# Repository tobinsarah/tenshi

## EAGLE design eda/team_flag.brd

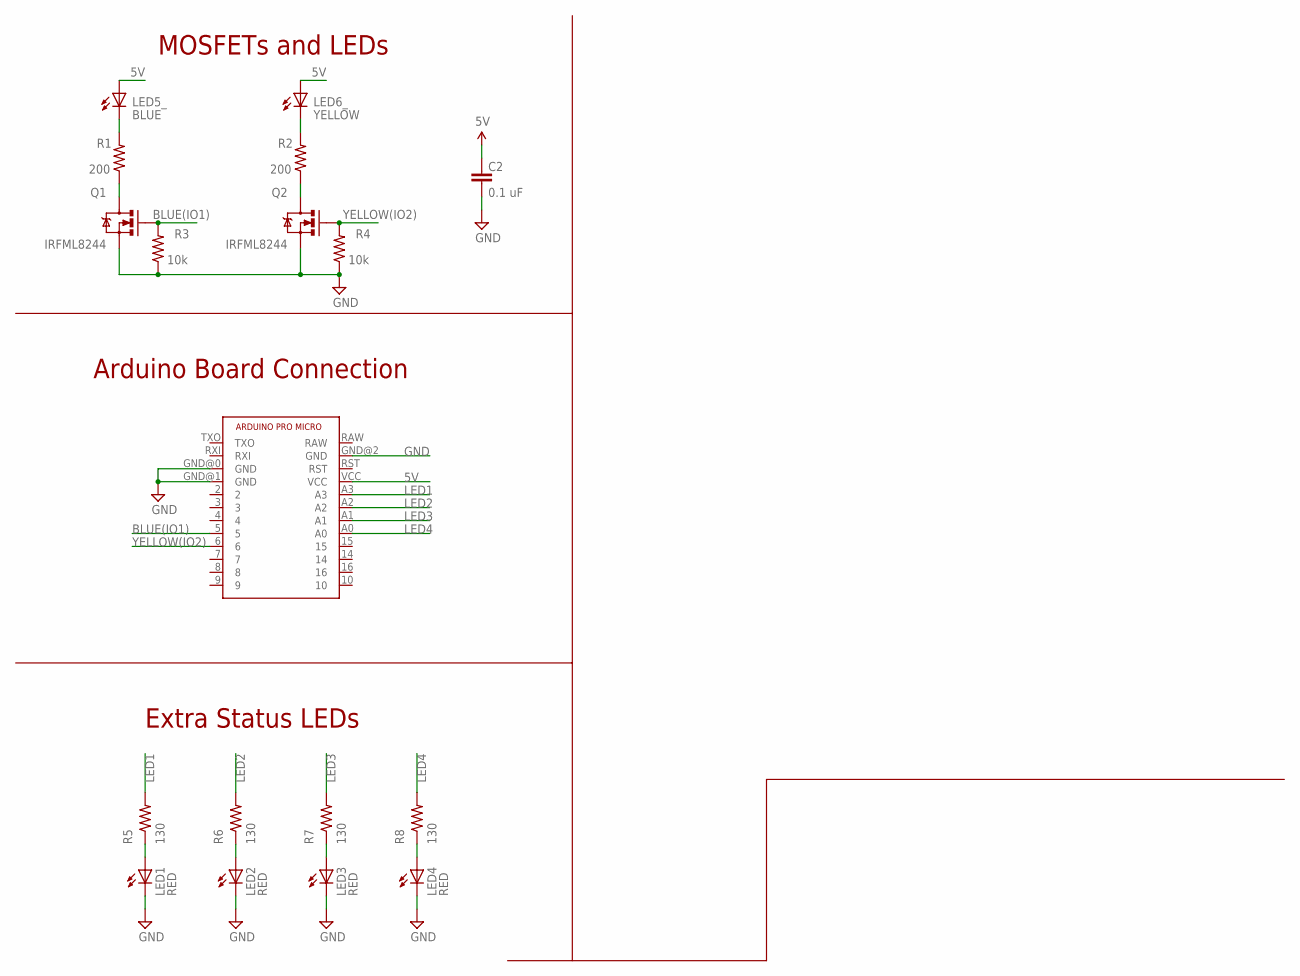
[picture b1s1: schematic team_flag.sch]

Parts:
C2: 0.1 uF; 0603-CAP
LED1, LED2, LED3, LED4: RED; LED-0805
LED5_: BLUE; LED5MM-NOFLAT
LED6_: YELLOW; LED5MM-NOFLAT
Q1, Q2: IRFML8244; SOT23-3
R1, R2: 200; R0603
R3, R4: 10k; R0603
R5, R6, R7, R8: 130; R0603
U$3: ARDUINO_PRO_MICRO

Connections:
5V: C2.1, LED5_.A, LED6_.A, U$3.VCC
BLUE(IO1): Q1.1 (G), R3.2, U$3.5
BSOURCE: Q1.3 (D), R1.1
GND: C2.2, LED1.C, LED2.C, LED3.C, LED4.C, Q1.2 (S), Q2.2 (S), R3.1, R4.1, U$3.GND@0 (GND), U$3.GND@1 (GND), U$3.GND@2 (GND)
LED1: R5.2, U$3.A3
LED1R: LED1.A, R5.1
LED2: R6.2, U$3.A2
LED2R: LED2.A, R6.1
LED3: R7.2, U$3.A1
LED3R: LED3.A, R7.1
LED4: R8.2, U$3.A0
LED4R: LED4.A, R8.1
unnamed: LED5_.K (C), R1.2
unnamed: LED6_.K (C), R2.2
YELLOW(IO2): Q2.1 (G), R4.2, U$3.6
YSOURCE: Q2.3 (D), R2.1

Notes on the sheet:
MOSFETs and LEDs
Extra Status LEDs
Arduino Board Connection

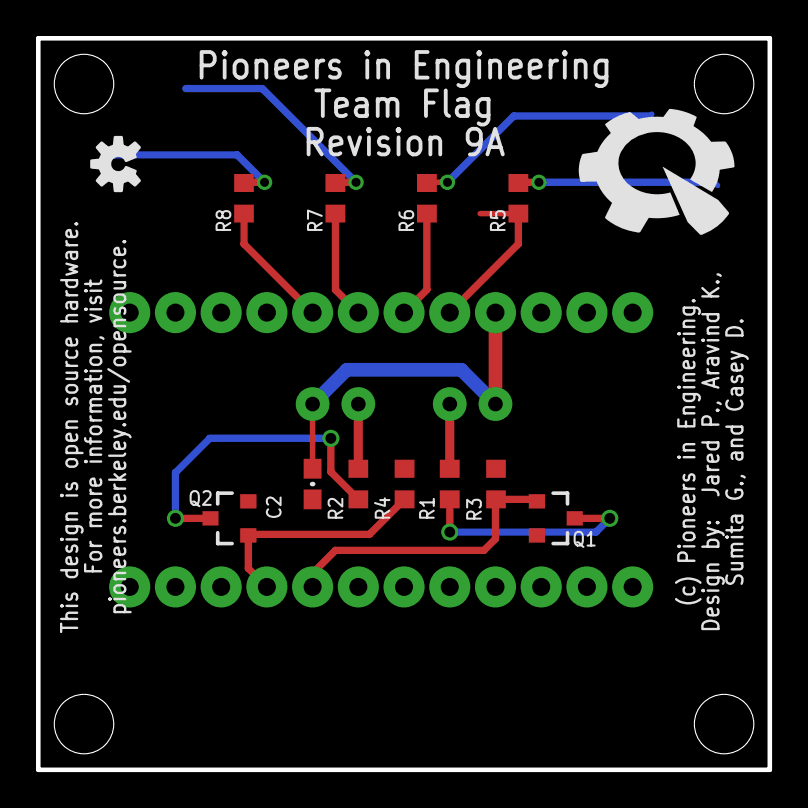
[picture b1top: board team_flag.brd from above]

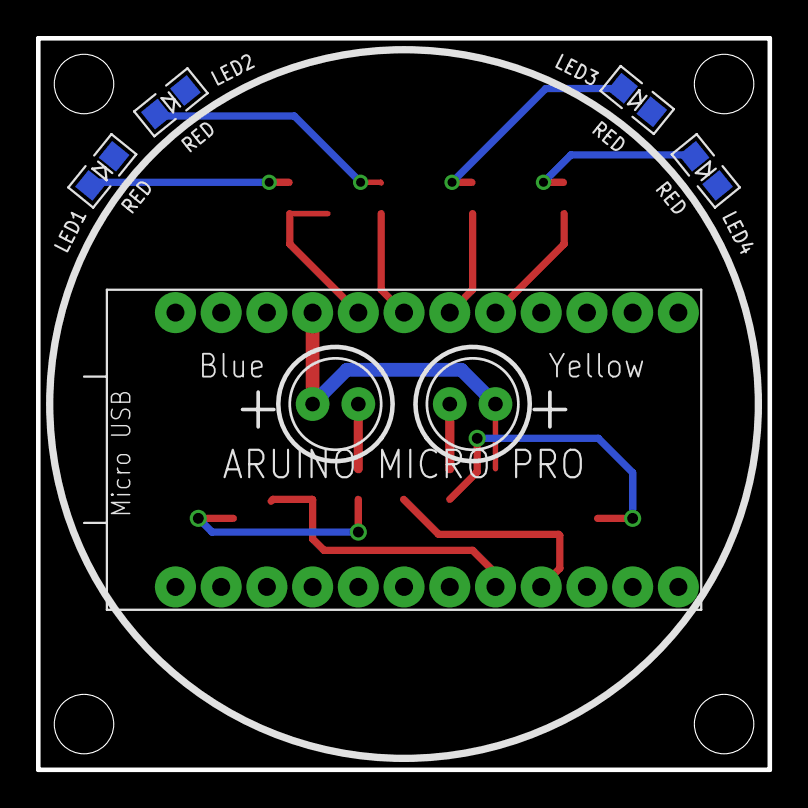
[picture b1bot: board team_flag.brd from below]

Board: 2 copper layers, 40.6 x 40.6 mm, 24 parts (7 on the bottom side), 16 nets.

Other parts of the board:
U$1: PIE-LOGO-SMALL
U$2: OSHW-LOGO-S
U$11, U$12, U$13, U$14: STAND-OFF

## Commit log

2016-07-01 Misc changes (should be reviewed more carefully and possibly deleted)
2016-09-24 Add Arduino Pro Micro breakout and connect nets on schematic
2016-09-24 Finished routing team flag board (now with Arduino ProMicro)
2016-09-24 Update revision info for Team Flag
